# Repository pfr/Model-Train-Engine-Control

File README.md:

# Model-Train-Engine-Control
If you're a DIYer who enjoys model trains and hobbiest level electronics, and would like to convert your model train engines to radio control and battery power, then this material is for you.

.

Code and other material here was created by me to convert my O scale engines to radio control and battery power.  Seen above is a 1999 MTH NW-2 (https://www.mthtrains.com/products/30-2157-1), one of my smaller engines, with control logic I created and LiPo battery power that can run the engine for hours.  With this accomplishment I'm certain the remainder of my O scale engines can be converted similarly.  There's enough information here to support your doing the same kind of conversions: all of my supporting code, KiCAD design files for a custom PCB, and FreeCAD  design files for 3D printed parts.  

An article on this effort will appear in an upcoming issue of Model Railroader Magazine (https://www.trains.com/mrr/) in early 2026. 

2025 12 05: A reasonably detailed instruction manual for the material here will follow soon.

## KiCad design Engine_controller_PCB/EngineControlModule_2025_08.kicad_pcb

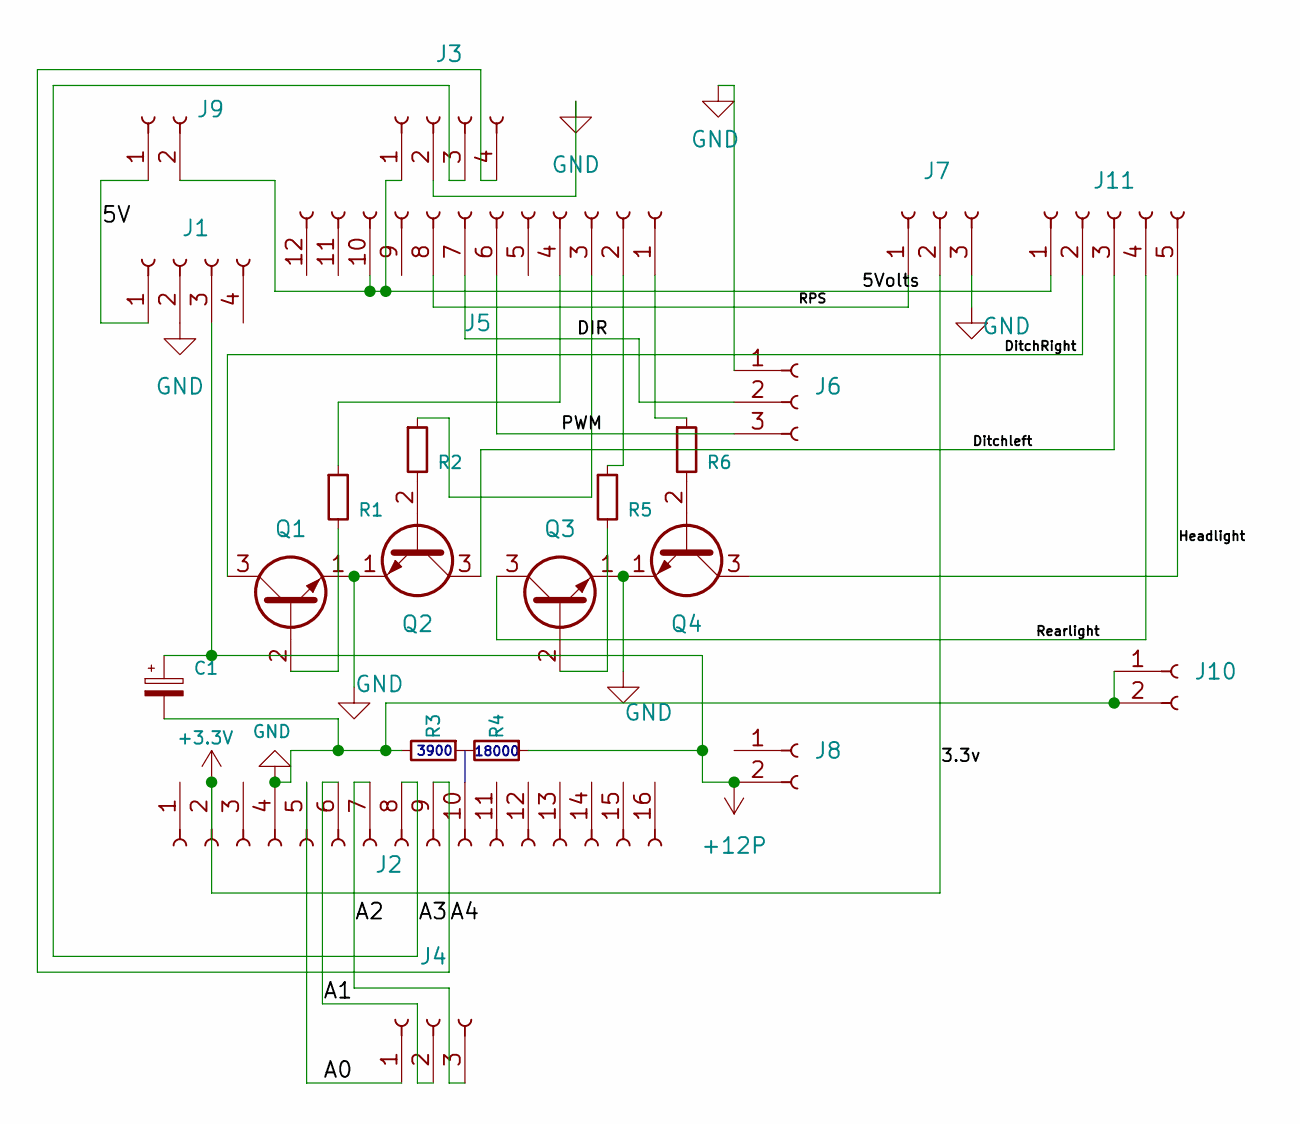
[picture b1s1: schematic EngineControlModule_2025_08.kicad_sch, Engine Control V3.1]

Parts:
C1: C_Polarized_Small; CP_Radial_D5.0mm_P2.50mm
J1: Conn_01x04_Socket; PinSocket_1x04_P2.54mm_Vertical
J2: Conn_01x16_Socket; PinSocket_1x16_P2.54mm_Vertical
J3: Conn_01x04_Socket; Molex_KK-254_AE-6410-04A_1x04_P2.54mm_Vertical
J4, J6: Conn_01x03_Socket; PinSocket_1x03_P2.54mm_Vertical
J5: Conn_01x12_Socket; PinSocket_1x12_P2.54mm_Vertical
J7: Conn_01x03_Socket; Molex_KK-254_AE-6410-03A_1x03_P2.54mm_Vertical
J8, J9, J10: Conn_01x02_Socket; PinSocket_1x02_P2.54mm_Vertical
J11: Conn_01x05_Socket; Molex_KK-254_AE-6410-05A_1x05_P2.54mm_Vertical
Q1, Q2, Q3, Q4: PN2222A; TO-92_Inline
R1, R2, R3, R4, R5, R6: R_Small; R_Axial_DIN0207_L6.3mm_D2.5mm_P7.62mm_Horizontal

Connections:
+3.3V: J2.2, J7.2
+12P: C1.1, J1.3, J8.2, R4.1
/5V: J1.1, J9.1
/5Volts: J3.1, J5.10, J9.2, J11.1
/A0: J2.5, J4.1
/A1: J2.6, J4.2
/A2: J2.7, J4.3
/A3: J2.8, J3.3
/A4: J2.9, J3.4
/DIR: J5.7, J6.2
/DitchRight: J11.2, Q1.3 (C)
/Ditchleft: J11.3, Q2.3 (C)
/Headlight: J11.5, Q4.3 (C)
/PWM: J5.6, J6.3
/RPS: J5.8, J7.1
/Rearlight: J11.4, Q3.3 (C)
GND: C1.2, J1.2, J2.4, J3.2, J6.1, J7.3, J10.1, J10.2, Q1.1 (E), Q2.1 (E), Q3.1 (E), Q4.1 (E), R3.2
unnamed: J5.1, R6.1
unnamed: J5.2, R5.1
unnamed: J5.3, R2.1
unnamed: J5.4, R1.1
unnamed: Q1.2 (B), R1.2
unnamed: Q2.2 (B), R2.2
unnamed: Q3.2 (B), R5.2
unnamed: Q4.2 (B), R6.2

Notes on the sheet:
3900
18000

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
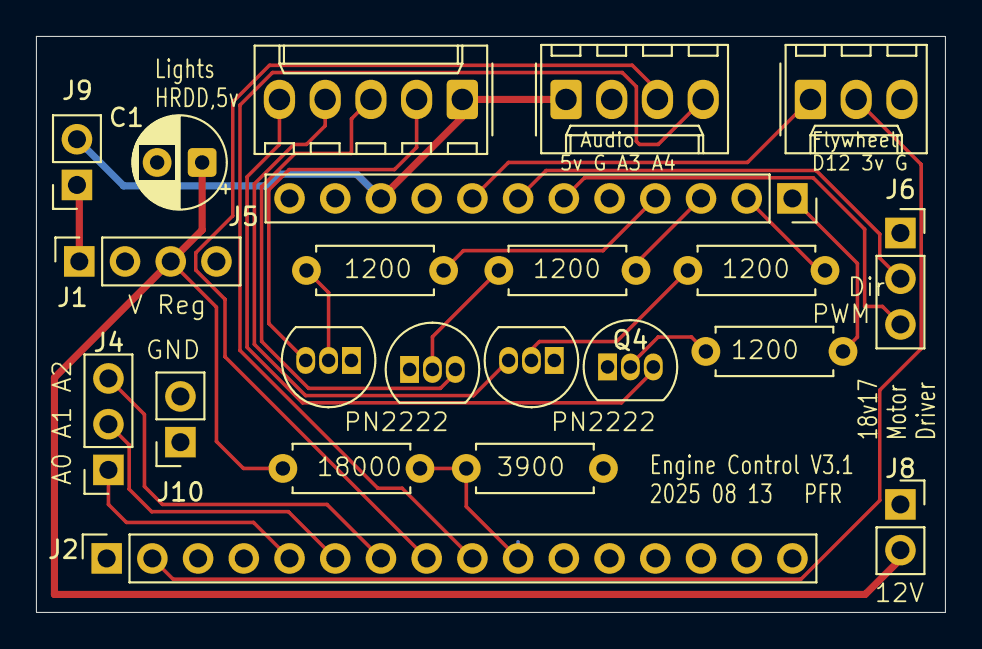
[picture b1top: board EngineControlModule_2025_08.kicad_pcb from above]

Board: 2 copper layers, 50.5 x 32.0 mm, 22 parts (0 on the bottom side), 26 nets.

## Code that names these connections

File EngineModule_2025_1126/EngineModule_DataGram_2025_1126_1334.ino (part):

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uint16_t RPS[23];  // Create bins for target flywheel rotations per second, indexed by requested speeds.  Bins represent
                   //  values 5 MPH apart.  RPS[0] is for zero MPH, RPS[1] is for 0 MPH,...  RPS[21] is for 100 MPH.
                   //  RPS[22] is a sentinel == to RPS[21].
uint16_t desiredRPS = 0;  // target RPS derived from a requested speed setting;
uint8_t maxPowerDelta = 0;


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}

int RPSErrorSum = 0;  //  Used in support of PID motor control done in updateSpeedSetting()
uint8_t Kp = 0;  //        Kp is used to scale and normalize updates from RPS to PWM percent
uint8_t Ki = 0;  //       Ki is used to scale and normalize updates from RPS to PWM percent
uint8_t Kd = 0;  //       Kd is used to scale and normalize updates from RPS to PWM percent

void updateSpeedSetting(){
// smoothedRPS is the RC filtered pulse count most recently computed during latest TCC2 interrupt
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      for (byte i =1; i < 22; i++)
        RPS[i] = 10*buf[i + dataLoc +2];  // Save rotations per second indexed by increments of 5MPH
                                // bytes received have been divided by ten to fit in a byte each for transmission.
      RPS[0] = 0;         // lower end sentinel for interpolation
      RPS[22] = RPS[21];  // upper end sentinel for interpolation
      if(DEBUG){ Serial.println("Motor control is set to cruise.");}
      speedControlMethod = cruise;  // Motor control will be done based on submitted speeds.
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	    if(DEBUG){ Serial.print("start up idle engine requested:  ");    Serial.println(myAddress);}
      // Startup command passes GPIO numbers for light control
      headlight = buf[dataLoc];  rearlight = buf[dataLoc+1];  leftDitch = buf[dataLoc+2];    rightDitch = buf[dataLoc+3];
//      headlight = A0;  rearlight = A1;  leftDitch = A2;    rightDitch = A3;
      pinMode(headlight, OUTPUT);    pinMode(rearlight, OUTPUT);   pinMode(leftDitch, OUTPUT);   pinMode(rightDitch, OUTPUT);

      if(DEBUG){ Serial.print("Headlight: "); Serial.println(headlight);}

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              for (byte i =1; i < 22; i++)
                RPS[i] = 10*buf[i + dataLoc +2];  // Save rotations per second indexed by increments of 5MPH
                                        // bytes received have been divided by ten to fit in a byte each for transmission.
              RPS[0] = 0;         // lower end sentinel for interpolation
              RPS[22] = RPS[21];  // upper end sentinel for interpolation
        }
        if (speedControlMethod == cruise) // Engine started up and in cruise -> need to refresh requested speed
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
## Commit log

2025-12-04 Added readme
2025-12-04 Getting images to work in readme
2025-12-04 still trying images
2025-12-04 images are a challenge
2025-12-05 ChatGPT says this this attempt to load an image should work.
2025-12-05 3D, PCB and schematic added
2025-12-05 Corrected typo in readme
2025-12-05 Added MRR reference
2025-12-05 Added MTH URL
